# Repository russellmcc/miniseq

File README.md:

# MiniSeq

This is a nascent design for a trim-pot eurorack sequencer

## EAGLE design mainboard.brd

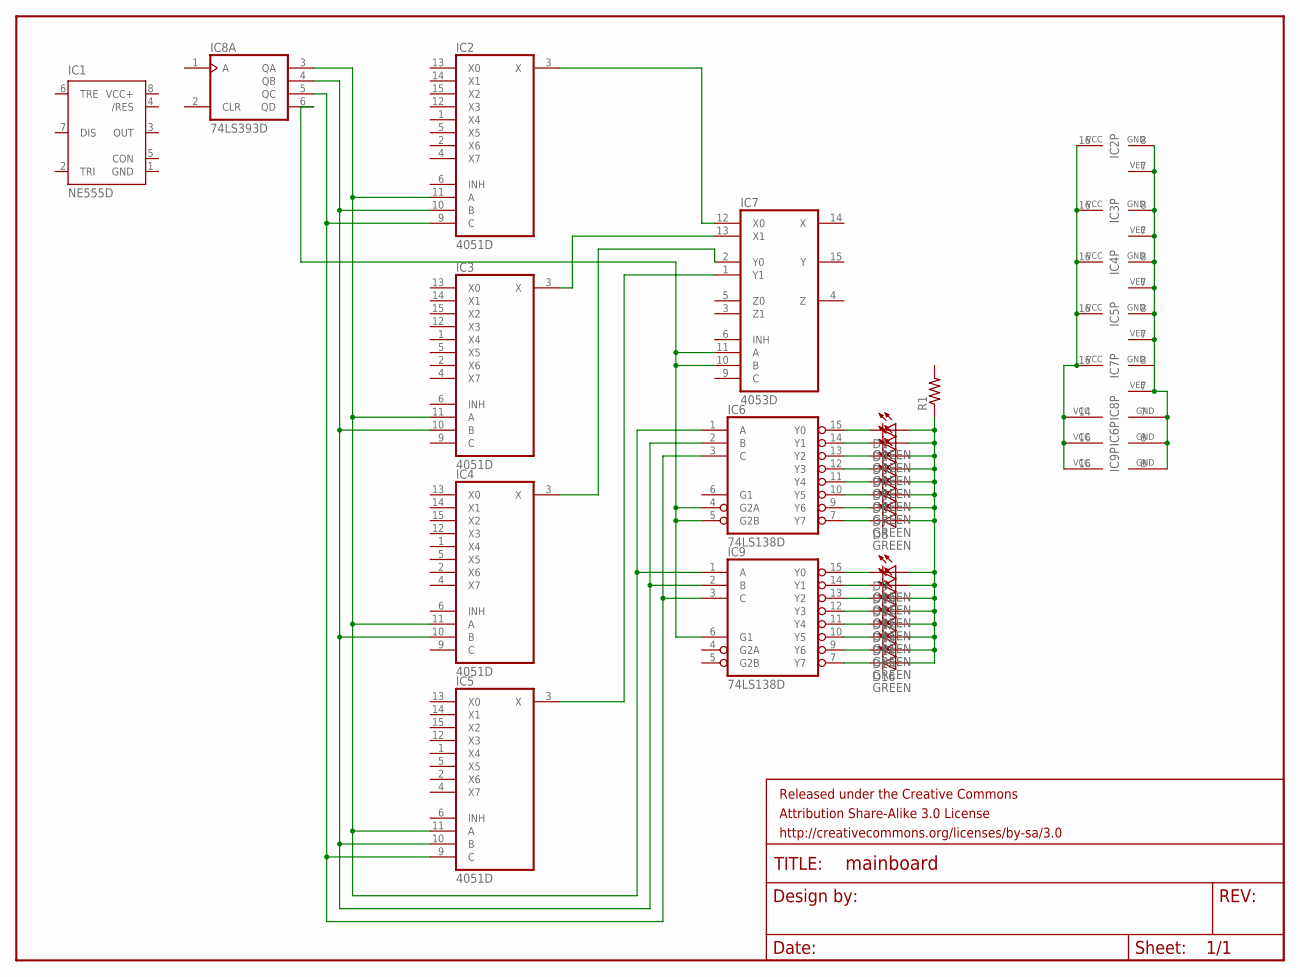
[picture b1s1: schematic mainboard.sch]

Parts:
D1, D2, D3, D4, D5, D6, D7, D8, D9, D10, D11, D12, D13, D14, D15, D16: GREEN; LED-0603
FRAME1: FRAME-LETTER; CREATIVE_COMMONS
IC1: NE555D; SO08
IC2, IC3, IC4, IC5: 4051D; SO16
IC6, IC9: 74LS138D; SO16
IC7: 4053D; SO16
IC8: 74LS393D; SO14
R1: RESISTOR0603; 0603-RES

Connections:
GND: IC1.1 (GND), IC7.8 (GND)
unnamed: IC2.7 (VEE), IC2.8 (GND), IC3.7 (VEE), IC3.8 (GND), IC4.7 (VEE), IC4.8 (GND), IC5.7 (VEE), IC5.8 (GND), IC6.8 (GND), IC7.7 (VEE), IC8.7 (GND), IC9.8 (GND)
unnamed: IC2.16 (VCC), IC3.16 (VCC), IC4.16 (VCC), IC5.16 (VCC), IC6.16 (VCC), IC7.16 (VCC), IC8.14 (VCC), IC9.16 (VCC)
unnamed: IC2.11 (A), IC3.11 (A), IC4.11 (A), IC5.11 (A), IC6.1 (A), IC8.3 (QA), IC9.1 (A)
unnamed: IC2.10 (B), IC3.10 (B), IC4.10 (B), IC5.10 (B), IC6.2 (B), IC8.4 (QB), IC9.2 (B)
unnamed: IC2.9 (C), IC5.9 (C), IC6.3 (C), IC8.5 (QC), IC9.3 (C)
unnamed: IC6.4 (G2A), IC6.5 (G2B), IC7.10 (B), IC7.11 (A), IC8.6 (QD), IC9.6 (G1)
unnamed: IC2.3 (X), IC7.12 (X0)
unnamed: IC3.3 (X), IC7.13 (X1)
unnamed: IC4.3 (X), IC7.2 (Y0)
unnamed: IC5.3 (X), IC7.1 (Y1)
unnamed: D1.C, IC6.15 (Y0)
unnamed: D2.C, IC6.14 (Y1)
unnamed: D3.C, IC6.13 (Y2)
unnamed: D4.C, IC6.12 (Y3)
unnamed: D5.C, IC6.11 (Y4)
unnamed: D6.C, IC6.10 (Y5)
unnamed: D7.C, IC6.9 (Y6)
unnamed: D8.C, IC6.7 (Y7)
unnamed: D9.C, IC9.15 (Y0)
unnamed: D10.C, IC9.14 (Y1)
unnamed: D11.C, IC9.13 (Y2)
unnamed: D12.C, IC9.12 (Y3)
unnamed: D13.C, IC9.11 (Y4)
unnamed: D14.C, IC9.10 (Y5)
unnamed: D15.C, IC9.9 (Y6)
unnamed: D16.C, IC9.7 (Y7)
unnamed: D1.A, D2.A, D3.A, D4.A, D5.A, D6.A, D7.A, D8.A, D9.A, D10.A, D11.A, D12.A, D13.A, D14.A, D15.A, D16.A, R1.1
VCC+: IC1.8 (VCC+)

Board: 2 copper layers, 27 parts (0 on the bottom side), 28 nets, no tracks yet.

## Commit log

2013-09-14 initial.
2013-09-14 added stub BOM
2013-09-14 added diodes

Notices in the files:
parts and their libraries:
SparkFun-Aesthetics: Licensing: CC v3.0 Share-Alike You are welcome to use this library for commercial purposes.
SparkFun-Aesthetics: Released under the Creative Commons Attribution Share-Alike 3.0 License
SparkFun-Aesthetics: http://creativecommons.org/licenses/by-sa/3.0
